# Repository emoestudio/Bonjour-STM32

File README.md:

## Bonjour STM32~  

本系列教程帮助您快速上手stm32CubeMX + MDK5开发环境，并且使用HAL库快速开发stm32~  

## 仓库内容  

包含如下内容:  

- 我们编写的HAL库的基本例程代码(MDK5 Project)(位于HAL_Demo中)  
- 我们设计的STM32F401RCT6开发板的KiCad工程文件(位于Dev_Board/Hardware中)  
- 上面那块开发板的一些例程代码(位于Dev_Board/Software中)    

教程位于 **[我们的网站](https://www.emoe.xyz/archives/970)** 上,同时有几个视频发布在bilibili,链接如下:  

- [开发环境安装及配置](https://www.bilibili.com/video/BV1Lg4y1B7Bf/)  
- [使用KiCad设计电路板](https://www.bilibili.com/video/BV1Kp4y1X7pS/)  

暂时这样咯 ~咕咕~  

# 提示

如果你访问Github有困难，或者下载不下来，请到Gitee上下载我们的镜像源:  
https://gitee.com/emoestudio/Bonjour-STM32

Github源项目地址:  
https://github.com/emoestudio/Bonjour-STM32

# 我们的微信公众号

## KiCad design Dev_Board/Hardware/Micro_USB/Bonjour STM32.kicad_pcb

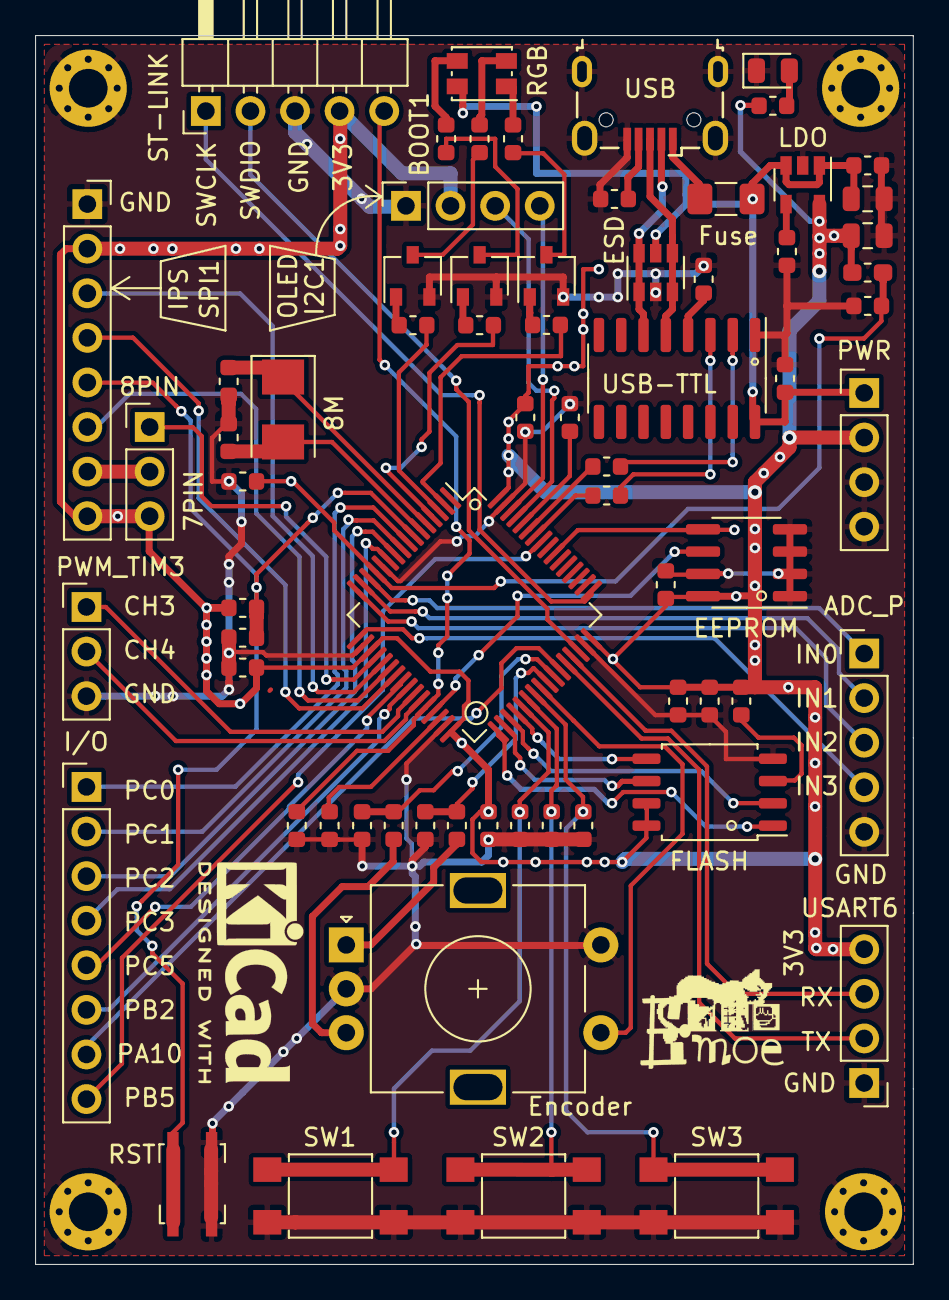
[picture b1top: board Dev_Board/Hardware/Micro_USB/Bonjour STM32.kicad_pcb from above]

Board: 2 copper layers, 50.0 x 70.0 mm, 72 parts (0 on the bottom side), 73 nets.

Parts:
8M: 8M; Crystal_SMD_5032-2Pin_5.0x3.2mm
C0: 2.2u; C_0603_1608Metric
C1, C3, C4, C5, C6, C10, C12, C13, C14, C15, C16, C17, C18, C19, C20, C21, C22: 104; C_0603_1608Metric
C2, C9: 10u; C_0805_2012Metric
C7: 103; C_0603_1608Metric
C8, C11: 22p; C_0603_1608Metric
D1: LED; LED_0805_2012Metric
D2: LED_RABG; LED_Kingbright_AAA3528ESGCT
F1: 5V_2A; Fuse_1206_3216Metric_Pad1.42x1.75mm_HandSolder
H1, H2, H3, H4: Stand; MountingHole_2.2mm_M2_Pad_Via
J1: USB_B_Micro; USB_Micro-B_Wuerth_629105150521
J2: ADC; PinHeader_1x05_P2.54mm_Vertical
J3: PWM; PinHeader_1x03_P2.54mm_Vertical
J5: GPIO; PinHeader_1x08_P2.54mm_Vertical
J6: USART6; PinHeader_1x04_P2.54mm_Vertical
J7: IPS_ST7789; PinSocket_1x08_P2.54mm_Vertical
J8: OLED_SSD1306; PinSocket_1x04_P2.54mm_Vertical
J11: IPS_SWITCH; PinHeader_1x03_P2.54mm_Vertical
J12: 5V; PinHeader_1x04_P2.54mm_Vertical
J13: ST-LINK; PinHeader_1x05_P2.54mm_Horizontal
L1: 47uH; L_0603_1608Metric_Pad1.05x0.95mm_HandSolder
Q1, Q2, Q3: S8050-SOT23; SOT-23W
R0, R3, R4, R14, R15: 10k; R_0603_1608Metric
R1, R2, R5, R6, R7, R8, R9, R10, R11: 1k; R_0603_1608Metric
R12, R13: 4.7k; R_0603_1608Metric
SW1, SW2, SW3: SW_Push; SW_SPST_TL3305C
SW4: SW_Push; Button_SMD_3mmx4mmx2.5mm
SW5: Rotary_Encoder_Switch; RotaryEncoder_Alps_EC11E-Switch_Vertical_H20mm
U1: CH340G; SOIC-16_3.9x9.9mm_P1.27mm
U2: RT9193-3.3; SOT-23-5
U3: STM32F401RCTx; LQFP-64_10x10mm_P0.5mm
U4: W25Q128JVS; SOIC-8_5.23x5.23mm_P1.27mm
U5: M24C02-FMN; SOIC-8_3.9x4.9mm_P1.27mm
U6: USBLC6-2SC6; SOT-23-6

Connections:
+3V3: C9.1, C15.1, C16.1, C17.1, C18.1, C20.1, C21.1, J6.4, J7.2, J7.8, J8.2, J11.3, J12.2, J13.4, L1.1, R1.1, R2.1, R11.1, U2.5, U3.19, U3.32, U3.48, U3.64, U4.7, U4.8, U5.8
+5V: C2.1, C6.1, C22.2, D2.2, F1.2, J12.1, U1.16, U2.1, U2.3, U6.5
/ADC1_IN0: J2.1, U3.14
/ADC1_IN1: J2.2, U3.15
/ADC1_IN2: J2.3, U3.16
/ADC1_IN3: J2.4, U3.17
/BOOT0: R0.1, U3.60
/BOOT1: J13.5, R15.1, U3.28
/CS|BLK: J7.7, J11.2
/ENCODER_KEY: SW5.S1, U3.40
/I2C1_SCL: J8.3, U3.61
/I2C1_SDA: J8.4, U3.62
/I2C2_SCL: U3.29, U5.6
/I2C2_SDA: U3.55, U5.5
/KEY1: C3.2, SW1.2, U3.37
/KEY2: C4.2, SW2.2, U3.38
/KEY3: C5.2, SW3.2, U3.39
/NRST: C10.1, J7.5, R1.2, SW4.2, U3.7
/PA10: J5.7, U3.43
/PB5: J5.8, U3.57
/PC0: J5.1, U3.8
/PC1: J5.2, U3.9
/PC2: J5.3, U3.10
/PC3: J5.4, U3.11
/PC4: J5.5, U3.24
/PC5: J5.6, U3.25
/RGB_1: R5.2, U3.2
/RGB_2: R6.2, U3.3
/RGB_3: R10.2, U3.4
/SPI1_CS: J11.1, U3.20
/SPI1_DC: J7.6, U3.22
/SPI1_MOSI: J7.4, U3.23
/SPI1_SCK: J7.3, U3.21
/SPI2_CS: U3.33, U4.1
/SPI2_MISO: U3.35, U4.2
/SPI2_MOSI: U3.36, U4.5
/SPI2_SCK: U3.34, U4.6
/SWCLK: J13.1, U3.49
/SWDIO: J13.2, U3.46
/TIM1_CH1: C13.2, R3.2, U3.41
/TIM1_CH2: C14.1, R4.2, U3.42
/TIM3_CH3: J3.1, U3.26
/TIM3_CH4: J3.2, U3.27
/USART1_RX: R13.2, U3.59
/USART1_TX: R12.2, U3.58
/USART6_RX: J6.3, U3.45
/USART6_TX: J6.2, U3.44
/USB_DN: J1.2, U1.6, U6.1, U6.6
/USB_DP: J1.3, U1.5, U6.3, U6.4
/XTAL_IN: 8M.1, C8.1, U3.5
/XTAL_OUT: 8M.2, C11.1, U3.6
GND: C0.2, C1.2, C2.2, C3.1, C4.1, C5.1, C6.2, C7.2, C8.2, C9.2, C10.2, C11.2, C12.2, C13.1, C14.2, C15.2, C16.2, C17.2, C18.2, C19.2, C20.2, C21.2, C22.1, D1.1, H1.1, H2.1, H3.1, H4.1, J1.5, J1.6, J2.5, J3.3, J6.1, J7.1, J8.1, J12.3, J12.4, J13.3, Q1.2, Q2.2, Q3.2, R0.2, R14.2, R15.2, SW1.1, SW2.1, SW3.1, SW4.1, SW5.C, SW5.S2, U1.1, U2.2, U3.12, U3.18, U3.31, U3.47, U3.63, U4.4, U5.1, U5.2, U5.3, U5.4, U5.7, U6.2
unnamed: C0.1, U3.30
unnamed: C1.1, U1.4
unnamed: C7.1, U2.4
unnamed: D1.2, R2.2
unnamed: D2.1, R7.2
unnamed: D2.3, R9.2
unnamed: D2.4, R8.2
unnamed: F1.1, J1.1
unnamed: J1.4, R14.1
unnamed: Q1.1, R5.1
unnamed: Q1.3, R7.1
unnamed: Q2.1, R6.1
unnamed: Q2.3, R8.1
unnamed: Q3.1, R10.1
unnamed: Q3.3, R9.1
unnamed: R3.1, SW5.A
unnamed: R4.1, SW5.B
unnamed: R11.2, U4.3
unnamed: R12.1, U1.3
unnamed: R13.1, U1.2
VDDA: C12.1, C19.1, L1.2, U3.13

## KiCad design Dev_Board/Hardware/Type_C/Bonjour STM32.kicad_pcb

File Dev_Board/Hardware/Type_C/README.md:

# Notice!

Type-C version is never tested!  

Use it at your own risk XD

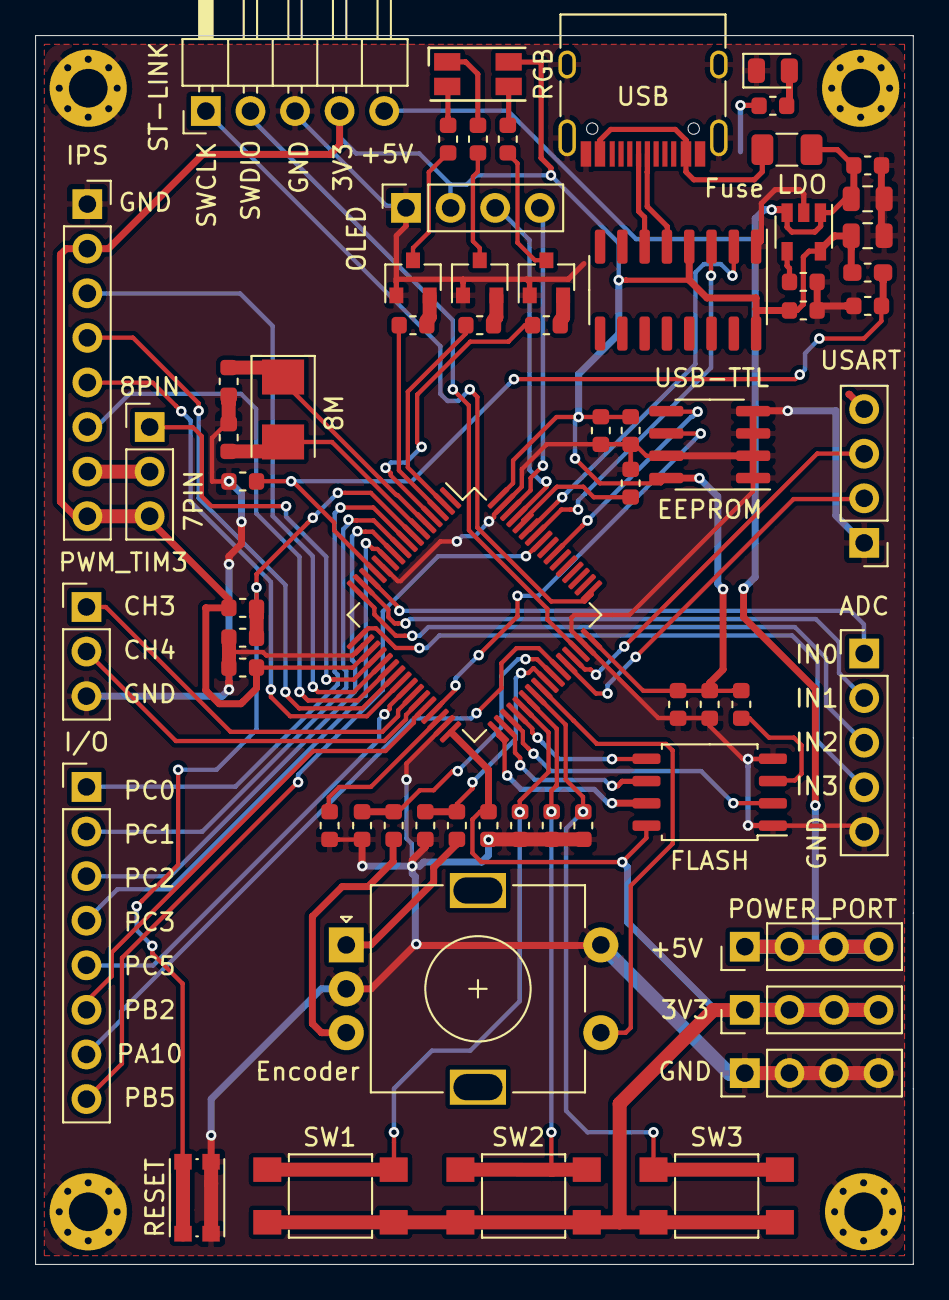
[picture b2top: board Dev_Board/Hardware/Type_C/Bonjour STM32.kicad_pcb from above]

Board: 2 copper layers, 50.0 x 70.0 mm, 68 parts (0 on the bottom side), 69 nets.

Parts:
3V3: 3V3; PinHeader_1x04_P2.54mm_Vertical
8M: 8M; Crystal_SMD_5032-2Pin_5.0x3.2mm
+5V: 5V; PinHeader_1x04_P2.54mm_Vertical
ADC: ADC; PinHeader_1x05_P2.54mm_Vertical
C0: 2.2u; C_0603_1608Metric
C1, C3, C4, C5, C6, C10, C12, C13, C14, C15, C16, C17, C18, C19, C20, C21: 104; C_0603_1608Metric
C2, C9: 10u; C_0805_2012Metric
C7: 103; C_0603_1608Metric
C8, C11: 22p; C_0603_1608Metric
D1: LED; LED_0805_2012Metric
EEPROM: M24C02-FMN; SOIC-8_3.9x4.9mm_P1.27mm
Encoder: Rotary_Encoder_Switch; RotaryEncoder_Alps_EC11E-Switch_Vertical_H20mm
FLASH: W25Q128JVS; SOIC-8_5.23x5.23mm_P1.27mm
Fuse: 5V_2A; Fuse_1206_3216Metric
GND: GND; PinHeader_1x04_P2.54mm_Vertical
H1, H2, H3, H4: Stand; MountingHole_2.2mm_M2_Pad_Via
I/O: GPIO; PinHeader_1x08_P2.54mm_Vertical
IPS: IPS_ST7789; PinSocket_1x08_P2.54mm_Vertical
J11: IPS_SWITCH; PinHeader_1x03_P2.54mm_Vertical
L1: 47uH; L_0603_1608Metric_Pad1.05x0.95mm_HandSolder
LDO: RT9193-3.3; SOT-23-5
OLED: OLED_SSD1306; PinSocket_1x04_P2.54mm_Vertical
PWM_TIM3: PWM; PinHeader_1x03_P2.54mm_Vertical
Q1, Q2, Q3: S8050; SOT-23
R0, R3, R4: 10k; R_0603_1608Metric
R1, R2, R5, R6, R7, R8, R9, R10, R11: 1k; R_0603_1608Metric
RESET: SW_Push; SW_Push_1P1T_NO_CK_KMR2
RGB: LED_RGBA; LED_RGB_1210
ST-LINK: ST-LINK; PinHeader_1x05_P2.54mm_Horizontal
SW1, SW2, SW3: SW_Push; SW_SPST_TL3305C
U3: STM32F401RCTx; LQFP-64_10x10mm_P0.5mm
USART: USART6; PinHeader_1x04_P2.54mm_Vertical
USB: USB_C_Plug_USB2.0; USB_C_Receptacle_HRO_TYPE-C-31-M-12
USB-TTL: CH340G; SOIC-16_3.9x9.9mm_P1.27mm

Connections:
+3V3: 3V3.1, 3V3.2, 3V3.3, 3V3.4, C1.1, C9.1, C15.1, C16.1, C17.1, C18.1, C20.1, C21.1, EEPROM.8, FLASH.8, IPS.2, IPS.8, J11.3, L1.1, LDO.5, OLED.2, R1.1, R2.1, R11.1, RGB.4, ST-LINK.4, SW1.1, SW2.1, SW3.1, U3.19, U3.32, U3.48, U3.64, USART.4, USB-TTL.4, USB-TTL.16
+5V: +5V.1, +5V.2, +5V.3, +5V.4, C2.1, C6.1, Fuse.2, LDO.1, LDO.3, ST-LINK.5
/ADC1_IN0: ADC.1, U3.14
/ADC1_IN1: ADC.2, U3.15
/ADC1_IN2: ADC.3, U3.16
/ADC1_IN3: ADC.4, U3.17
/BOOT0: R0.1, U3.60
/CS|BLK: IPS.7, J11.2
/ENCODER_KEY: Encoder.S1, U3.40
/I2C1_SCL: OLED.3, U3.61
/I2C1_SDA: OLED.4, U3.62
/I2C2_SCL: EEPROM.6, U3.29
/I2C2_SDA: EEPROM.5, U3.55
/KEY1: C3.2, SW1.2, U3.37
/KEY2: C4.2, SW2.2, U3.38
/KEY3: C5.2, SW3.2, U3.39
/NRST: C10.1, R1.2, RESET.2, U3.7
/PA10: I/O.7, U3.43
/PB2: I/O.6, U3.28
/PB5: I/O.8, U3.57
/PC0: I/O.1, U3.8
/PC1: I/O.2, U3.9
/PC2: I/O.3, U3.10
/PC3: I/O.4, U3.11
/PC5: I/O.5, U3.25
/RGB_1: R5.2, U3.2
/RGB_2: R6.2, U3.3
/RGB_3: R10.2, U3.4
/SPI1_CS: J11.1, U3.20
/SPI1_DC: IPS.6, U3.22
/SPI1_MOSI: IPS.4, U3.23
/SPI1_RST: IPS.5, U3.24
/SPI1_SCK: IPS.3, U3.21
/SPI2_HOLD: FLASH.7, U3.33
/SPI2_MISO: FLASH.2, U3.35
/SPI2_MOSI: FLASH.5, U3.36
/SPI2_SCK: FLASH.6, U3.34
/SWCLK: ST-LINK.1, U3.49
/SWDIO: ST-LINK.2, U3.46
/TIM1_CH1: C13.2, R3.2, U3.41
/TIM1_CH2: C14.1, R4.2, U3.42
/TIM3_CH3: PWM_TIM3.1, U3.26
/TIM3_CH4: PWM_TIM3.2, U3.27
/USART1_RX: U3.59, USB-TTL.2
/USART1_TX: U3.58, USB-TTL.3
/USART6_RX: U3.45, USART.3
/USART6_TX: U3.44, USART.2
/USB_DN: USB.A7, USB-TTL.6
/USB_DP: USB.A6, USB-TTL.5
/XTAL_IN: 8M.1, C8.1, U3.5
/XTAL_OUT: 8M.2, C11.1, U3.6
GND: ADC.5, C0.2, C1.2, C2.2, C3.1, C4.1, C5.1, C6.2, C7.2, C8.2, C9.2, C10.2, C11.2, C12.2, C13.1, C14.2, C15.2, C16.2, C17.2, C18.2, C19.2, C20.2, C21.2, D1.1, EEPROM.1, EEPROM.2, EEPROM.3, EEPROM.4, EEPROM.7, Encoder.C, Encoder.S2, FLASH.1, FLASH.4, GND.1, GND.2, GND.3, GND.4, H1.1, H2.1, H3.1, H4.1, IPS.1, LDO.2, OLED.1, PWM_TIM3.3, Q1.1, Q2.1, Q3.1, R0.2, RESET.1, ST-LINK.3, U3.12, U3.18, U3.31, U3.47, U3.63, USART.1, USB.A1, USB.A12, USB.B1, USB.B12, USB.S1, USB-TTL.1
unnamed: C0.1, U3.30
unnamed: C7.1, LDO.4
unnamed: D1.2, R2.2
unnamed: R7.2, RGB.1
unnamed: R8.2, RGB.2
unnamed: R9.2, RGB.3
unnamed: Fuse.1, USB.A4, USB.A9, USB.B4, USB.B9
unnamed: Q1.2, R5.1
unnamed: Q1.3, R7.1
unnamed: Q2.2, R6.1
unnamed: Q2.3, R8.1
unnamed: Q3.2, R10.1
unnamed: Q3.3, R9.1
unnamed: Encoder.A, R3.1
unnamed: Encoder.B, R4.1
unnamed: FLASH.3, R11.2
VDDA: C12.1, C19.1, L1.2, U3.13

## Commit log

2020-05-21 Add README
2020-05-21 Add demo 2&5 and PCB update
2020-06-07 Add Demo 04
2020-06-07 Add Demo 01 & delete trash files
2020-06-08 Fix GPIO_EXTI
2020-06-09 Update PCB design
2020-06-09 Update README to support Gitee
2020-06-11 fix footprint bug & add QR Code
2020-06-12 Fix Fatal Error on PCB Design
